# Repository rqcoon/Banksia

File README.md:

# Banksia

a 4x10 ortholinear bluetooth keyboard

bottom row is fixed 2x2 stabless (plate mount stabs possible)

[KLE link](http://www.keyboard-layout-editor.com/#/gists/ac4e33216322b06a96d62318165e8864)

this repo is just kicad files lol do whatever

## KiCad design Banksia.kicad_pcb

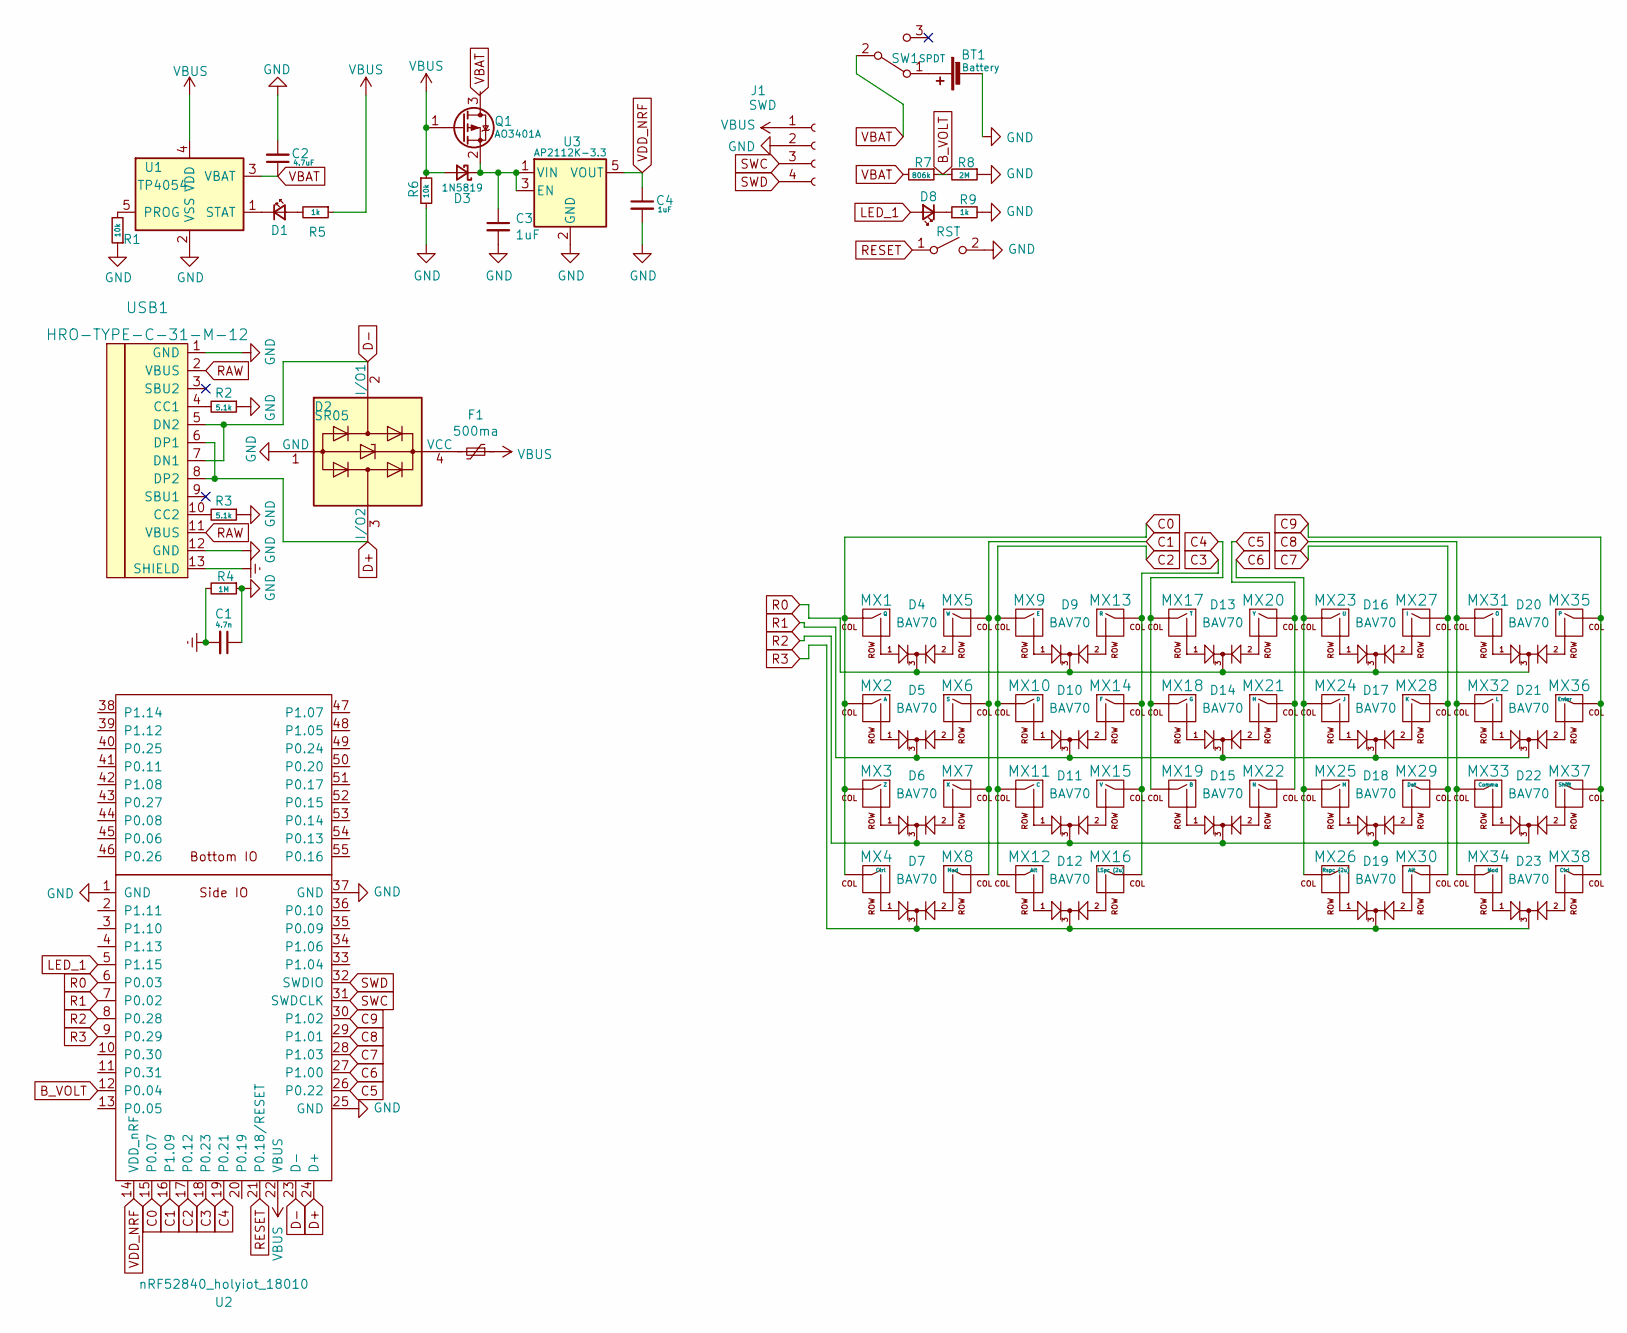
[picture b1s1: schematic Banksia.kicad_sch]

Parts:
BT1: Battery; JST_SH_BM02B-SRSS-TB_1x02-1MP_P1.00mm_Vertical
C1: 4.7n; C_1206_3216Metric
C2: 4.7uF; C_0805_2012Metric
C3, C4: 1uF; C_0805_2012Metric
D1: POWERLED; D_0805_2012Metric
D2: SR05; SOT-143
D3: 1N5819; D_SOD-123
D4, D5, D6, D7, D9, D10, D11, D12, D13, D14, D15, D16, D17, D18, D19, D20, D21, D22, D23: BAV70; SOT-23
D8: LED; D_0805_2012Metric
F1: 500ma; Fuse_1206_3216Metric
J1: SWD; PinHeader_1x04_P2.54mm_Vertical
MX1: Q; MXOnly-1U-NoLED
MX2: A; MXOnly-1U-NoLED
MX3: Z; MXOnly-1U-NoLED
MX4, MX38: Ctrl; MXOnly-1U-NoLED
MX5: W; MXOnly-1U-NoLED
MX6: S; MXOnly-1U-NoLED
MX7: X; MXOnly-1U-NoLED
MX8, MX34: Mod; MXOnly-1U-NoLED
MX9: E; MXOnly-1U-NoLED
MX10: D; MXOnly-1U-NoLED
MX11: C; MXOnly-1U-NoLED
MX12, MX30: Alt; MXOnly-1U-NoLED
MX13: R; MXOnly-1U-NoLED
MX14: F; MXOnly-1U-NoLED
MX15: V; MXOnly-1U-NoLED
MX16: LSpc (2u); MXOnly-1U-NoLED
MX17: T; MXOnly-1U-NoLED
MX18: G; MXOnly-1U-NoLED
MX19: B; MXOnly-1U-NoLED
MX20: Y; MXOnly-1U-NoLED
MX21: H; MXOnly-1U-NoLED
MX22: N; MXOnly-1U-NoLED
MX23: U; MXOnly-1U-NoLED
MX24: J; MXOnly-1U-NoLED
MX25: M; MXOnly-1U-NoLED
MX26: Rspc (2u); MXOnly-1U-NoLED
MX27: I; MXOnly-1U-NoLED
MX28: K; MXOnly-1U-NoLED
MX29: Dot; MXOnly-1U-NoLED
MX31: O; MXOnly-1U-NoLED
MX32: L; MXOnly-1U-NoLED
MX33: Comma; MXOnly-1U-NoLED
MX35: P; MXOnly-1U-NoLED
MX36: Enter; MXOnly-1U-NoLED
MX37: Shift; MXOnly-1U-NoLED
Q1: AO3401A; SOT-23
R1, R6: 10k; R_0805_2012Metric
R2, R3: 5.1k; R_0805_2012Metric
R4: 1M; R_0805_2012Metric
R5, R9: 1k; R_0805_2012Metric
R7: 806k; R_0805_2012Metric
R8: 2M; R_0805_2012Metric
SW1: SPDT; SW_CuK_OS102011MA1QN1_SPDT_Angled
SW2: RST; SW_SPST_SKQG_WithStem
U1: TP4054; SOT-23-5
U2: nRF52840_holyiot_18010
U3: AP2112K-3.3; SOT-23-5
USB1: HRO-TYPE-C-31-M-12; HRO-TYPE-C-31-M-12-Assembly

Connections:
B_VOLT: R7.1, R8.2, U2.12 (P0.04)
C0: MX1.1 (COL), MX2.1 (COL), MX3.1 (COL), MX4.1 (COL), U2.15 (P0.07)
C1: MX5.1 (COL), MX6.1 (COL), MX7.1 (COL), MX8.1 (COL), U2.16 (P1.09)
C2: MX9.1 (COL), MX10.1 (COL), MX11.1 (COL), MX12.1 (COL), U2.17 (P0.12)
C3: MX13.1 (COL), MX14.1 (COL), MX15.1 (COL), MX16.1 (COL), U2.18 (P0.23)
C4: MX17.1 (COL), MX18.1 (COL), MX19.1 (COL), U2.19 (P0.21)
C5: MX20.1 (COL), MX21.1 (COL), MX22.1 (COL), U2.26 (P0.22)
C6: MX23.1 (COL), MX24.1 (COL), MX25.1 (COL), MX26.1 (COL), U2.27 (P1.00)
C7: MX27.1 (COL), MX28.1 (COL), MX29.1 (COL), MX30.1 (COL), U2.28 (P1.03)
C8: MX31.1 (COL), MX32.1 (COL), MX33.1 (COL), MX34.1 (COL), U2.29 (P1.01)
C9: MX35.1 (COL), MX36.1 (COL), MX37.1 (COL), MX38.1 (COL), U2.30 (P1.02)
D+: D2.3 (I/O2), U2.24 (D+), USB1.6 (DP1), USB1.8 (DP2)
D-: D2.2 (I/O1), U2.23 (D-), USB1.5 (DN2), USB1.7 (DN1)
Earth: C1.2, R4.2, USB1.13 (SHIELD)
GND: BT1.2 (-), C1.1, C2.2, C3.2, C4.2, D2.1 (GND), J1.2, R1.1, R2.1, R3.1, R4.1, R6.2, R8.1, R9.2, SW2.2 (B), U1.2 (VSS), U2.1 (GND), U2.25 (GND), U2.37 (GND), U3.2 (GND), USB1.1 (GND), USB1.12 (GND)
LED_1: D8.2 (A), U2.5 (P1.15)
unnamed: BT1.1 (+), SW1.1 (A)
unnamed: C3.1, D3.1 (K), Q1.2 (S), U3.1 (VIN), U3.3 (EN)
unnamed: D1.1 (K), U1.1 (STAT)
unnamed: D1.2 (A), R5.2
unnamed: D2.4 (VCC), F1.2
unnamed: D4.1 (A1), MX1.2 (ROW)
unnamed: D4.2 (A2), MX5.2 (ROW)
unnamed: D5.1 (A1), MX2.2 (ROW)
unnamed: D5.2 (A2), MX6.2 (ROW)
unnamed: D6.1 (A1), MX3.2 (ROW)
unnamed: D6.2 (A2), MX7.2 (ROW)
unnamed: D7.1 (A1), MX4.2 (ROW)
unnamed: D7.2 (A2), MX8.2 (ROW)
unnamed: D8.1 (K), R9.1
unnamed: D9.1 (A1), MX9.2 (ROW)
unnamed: D9.2 (A2), MX13.2 (ROW)
unnamed: D10.1 (A1), MX10.2 (ROW)
unnamed: D10.2 (A2), MX14.2 (ROW)
unnamed: D11.1 (A1), MX11.2 (ROW)
unnamed: D11.2 (A2), MX15.2 (ROW)
unnamed: D12.1 (A1), MX12.2 (ROW)
unnamed: D12.2 (A2), MX16.2 (ROW)
unnamed: D13.1 (A1), MX17.2 (ROW)
unnamed: D13.2 (A2), MX20.2 (ROW)
unnamed: D14.1 (A1), MX18.2 (ROW)
unnamed: D14.2 (A2), MX21.2 (ROW)
unnamed: D15.1 (A1), MX19.2 (ROW)
unnamed: D15.2 (A2), MX22.2 (ROW)
unnamed: D16.1 (A1), MX23.2 (ROW)
unnamed: D16.2 (A2), MX27.2 (ROW)
unnamed: D17.1 (A1), MX24.2 (ROW)
unnamed: D17.2 (A2), MX28.2 (ROW)
unnamed: D18.1 (A1), MX25.2 (ROW)
unnamed: D18.2 (A2), MX29.2 (ROW)
unnamed: D19.1 (A1), MX26.2 (ROW)
unnamed: D19.2 (A2), MX30.2 (ROW)
unnamed: D20.1 (A1), MX31.2 (ROW)
unnamed: D20.2 (A2), MX35.2 (ROW)
unnamed: D21.1 (A1), MX32.2 (ROW)
unnamed: D21.2 (A2), MX36.2 (ROW)
unnamed: D22.1 (A1), MX33.2 (ROW)
unnamed: D22.2 (A2), MX37.2 (ROW)
unnamed: D23.1 (A1), MX34.2 (ROW)
unnamed: D23.2 (A2), MX38.2 (ROW)
unnamed: R1.2, U1.5 (PROG)
unnamed: R2.2, USB1.4 (CC1)
unnamed: R3.2, USB1.10 (CC2)
R0: D4.3 (K), D9.3 (K), D13.3 (K), D16.3 (K), D20.3 (K), U2.6 (P0.03)
R1: D5.3 (K), D10.3 (K), D14.3 (K), D17.3 (K), D21.3 (K), U2.7 (P0.02)
R2: D6.3 (K), D11.3 (K), D15.3 (K), D18.3 (K), D22.3 (K), U2.8 (P0.28)
R3: D7.3 (K), D12.3 (K), D19.3 (K), D23.3 (K), U2.9 (P0.29)
RAW: USB1.2 (VBUS), USB1.11 (VBUS)
RESET: SW2.1 (A), U2.21 (P0.18/RESET)
SWC: J1.3, U2.31 (SWDCLK)
SWD: J1.4, U2.32 (SWDIO)
VBAT: C2.1, R7.2, SW1.2 (B), U1.3 (VBAT)
VBUS: D3.2 (A), F1.1, J1.1, Q1.1 (G), R5.1, R6.1, U1.4 (VDD), U2.22 (VBUS)
VDD_NRF: C4.1, U2.14 (VDD_nRF), U3.5 (VOUT)

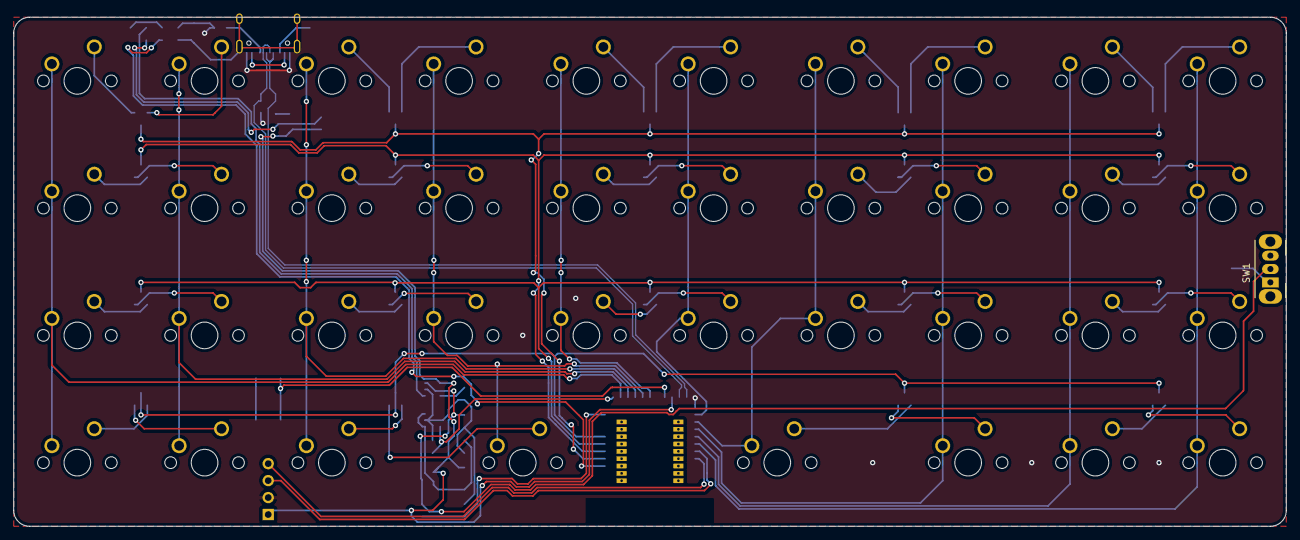
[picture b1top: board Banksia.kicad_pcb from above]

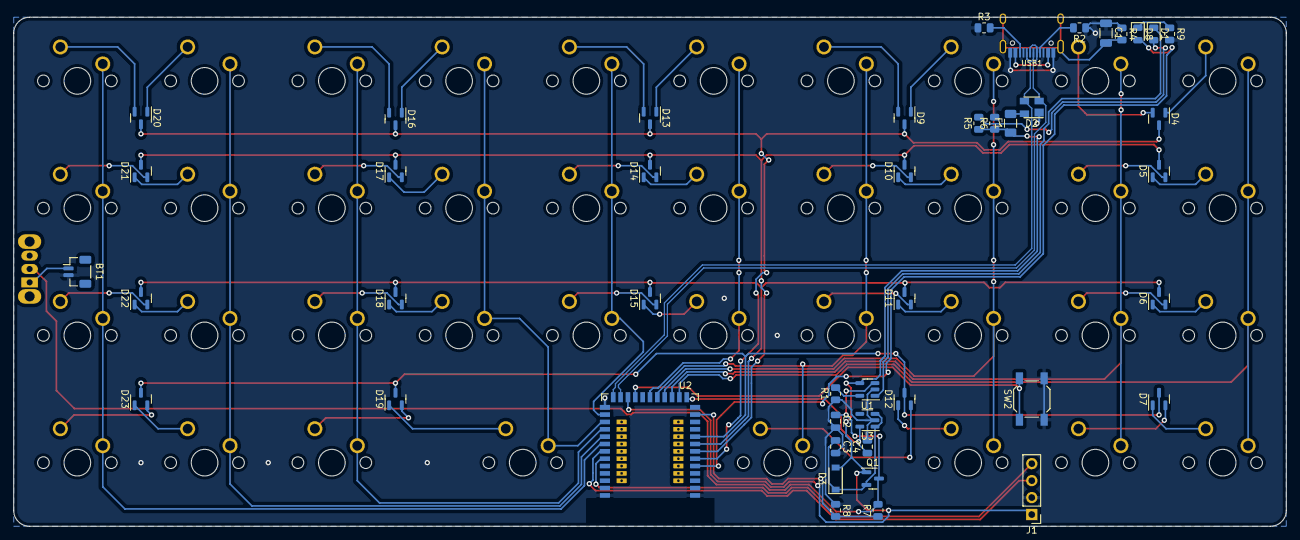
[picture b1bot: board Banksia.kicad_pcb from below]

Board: 2 copper layers, 190.5 x 76.2 mm, 84 parts (45 on the bottom side), 74 nets.
